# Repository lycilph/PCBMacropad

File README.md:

# PCBMacropad

Arduino pro micro pinout
* https://learn.sparkfun.com/tutorials/pro-micro--fio-v3-hookup-guide/hardware-overview-pro-micro
 
Kicad resources (for keyboards)
* https://github.com/joe-scotto/scottokeebs/tree/main/Extras/ScottoKicad
* https://github.com/ebastler/marbastlib

Tap drill chart (for self tapping screws into pla)
* https://mae.ufl.edu/designlab/Lab%20Assignments/EML2322L%20Tap%20Drill%20Chart.pdf
* From here: https://www.reddit.com/r/3dprinter/comments/fnlmps/hole_size_for_selftapping_screws/

Keycaps
* https://www.printables.com/model/109679-cherry-mx-low-profile-keycap
* https://www.thingiverse.com/thing:4186055
* https://www.printables.com/model/405230-blank-xda-keycap-mx-compatible
* https://www.printables.com/model/397962-blank-xda-profile-keycaps?ref=makerluis.com

Arduino simulator
* https://wokwi.com/projects/new/arduino-uno
* https://app.cirkitdesigner.com/

Idea for v2:
* https://github.com/dekuNukem/duckyPad-Pro

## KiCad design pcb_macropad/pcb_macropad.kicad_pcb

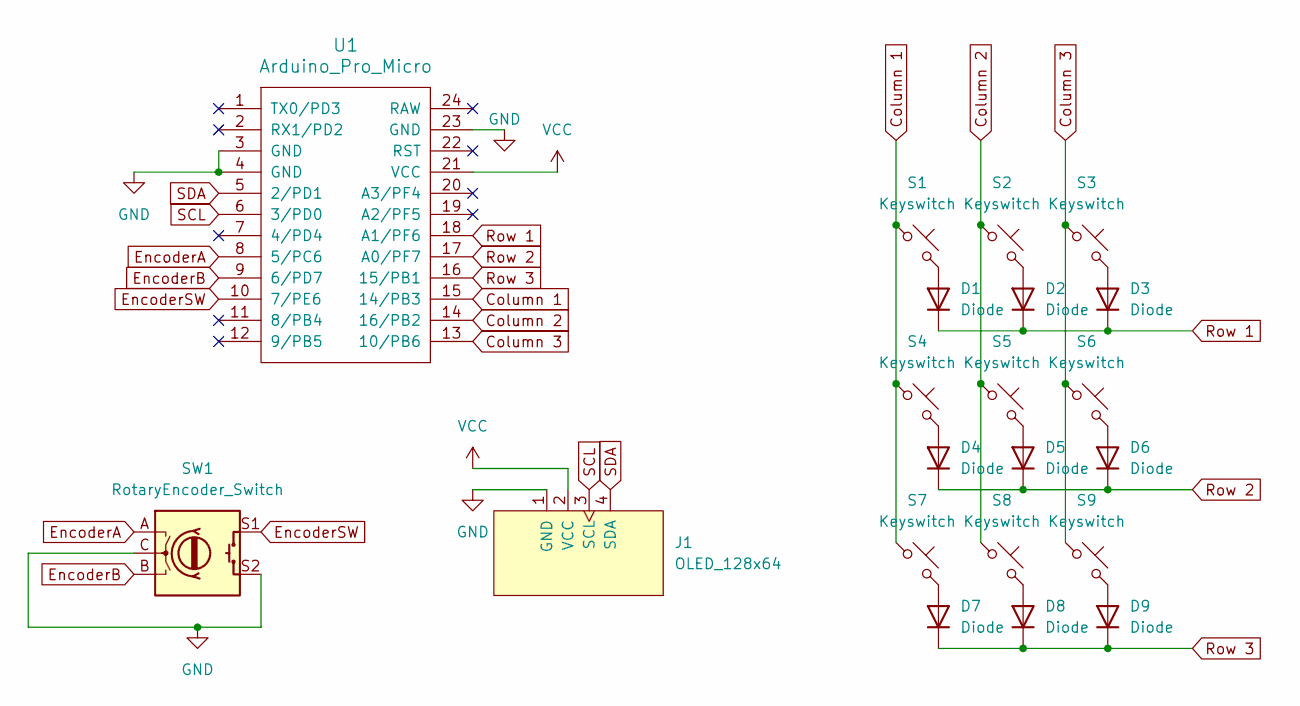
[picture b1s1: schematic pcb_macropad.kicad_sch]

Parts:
D1, D2, D3, D4, D5, D6, D7, D8, D9: Diode; Diode_DO-35
J1: OLED_128x64; 128x64OLED
S1, S2, S3, S4, S5, S6, S7, S8, S9: Keyswitch; MX_PCB_1.00u
SW1: RotaryEncoder_Switch; RotaryEncoder_Alps_EC11E-Switch_Vertical_H20mm
U1: Arduino_Pro_Micro

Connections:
Column 1: S1.1, S4.1, S7.1, U1.15 (14/PB3)
Column 2: S2.1, S5.1, S8.1, U1.14 (16/PB2)
Column 3: S3.1, S6.1, S9.1, U1.13 (10/PB6)
EncoderA: SW1.A, U1.8 (5/PC6)
EncoderB: SW1.B, U1.9 (6/PD7)
EncoderSW: SW1.S1, U1.10 (7/PE6)
GND: J1.1 (GND), SW1.C, SW1.S2, U1.3 (GND), U1.4 (GND), U1.23 (GND)
unnamed: D1.2 (A), S1.2
unnamed: D2.2 (A), S2.2
unnamed: D3.2 (A), S3.2
unnamed: D4.2 (A), S4.2
unnamed: D5.2 (A), S5.2
unnamed: D6.2 (A), S6.2
unnamed: D7.2 (A), S7.2
unnamed: D8.2 (A), S8.2
unnamed: D9.2 (A), S9.2
Row 1: D1.1 (K), D2.1 (K), D3.1 (K), U1.18 (A1/PF6)
Row 2: D4.1 (K), D5.1 (K), D6.1 (K), U1.17 (A0/PF7)
Row 3: D7.1 (K), D8.1 (K), D9.1 (K), U1.16 (15/PB1)
SCL: J1.3 (SCL), U1.6 (3/PD0)
SDA: J1.4 (SDA), U1.5 (2/PD1)
VCC: J1.2 (VCC), U1.21 (VCC)

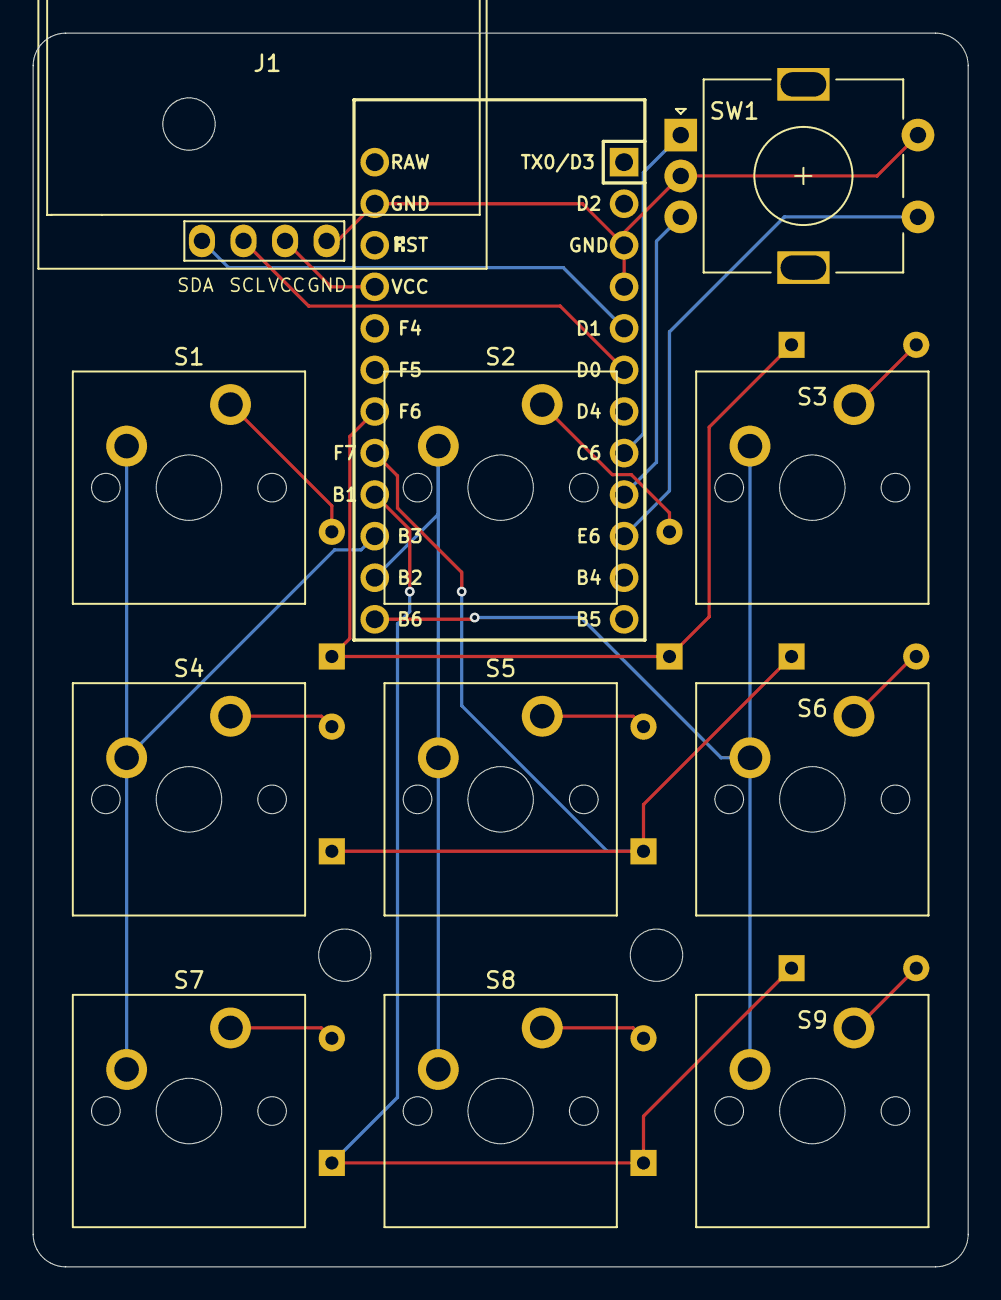
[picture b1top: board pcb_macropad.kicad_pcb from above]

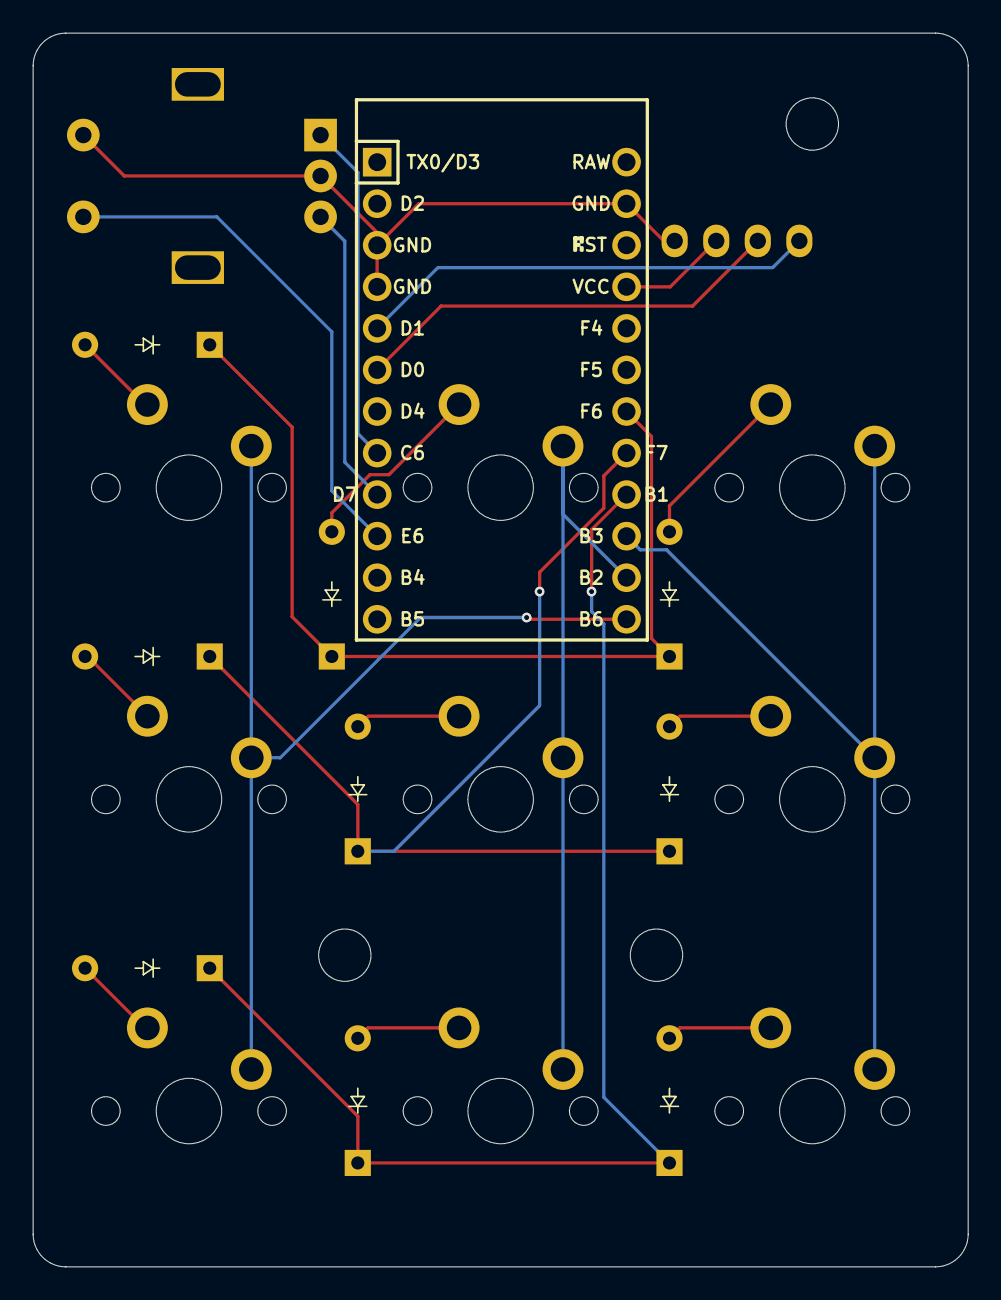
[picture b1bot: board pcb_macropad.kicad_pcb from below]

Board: 2 copper layers, 57.1 x 75.4 mm, 21 parts (10 on the bottom side), 22 nets.

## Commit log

2024-06-27 PCB draft done
2024-08-16 Backups
2024-08-19 Add burn in protection for the oled
2024-08-19 Graphics updated
2025-07-03 Making the macropad configurator app
2025-07-03 Added the traybar icon
2025-07-03 Added a log on the main winwo
2025-07-04 Working on the short edit view/view model
2025-07-04 Working on state management
2025-07-04 Loading data implemented
2025-07-04 Working on the shortcuts manager etc.
2025-07-08 Added the keyboardhook and adding/removing of shortcuts
2025-07-08 Making script compilation threaded
2025-07-08 Shortcut script compilation is not async
2025-07-08 Working on the configuration of the macropad buttons
2025-07-09 Added code for hid commucation
2025-07-09 Two-way communication via rawhid is now working
2025-07-10 Working on the macropad v2 firmware
2025-07-11 Working on the arduino v2 sketch
2025-07-12 Updating the arduino sketch
2025-07-12 Bugs in the sending of keys...
2025-07-15 V4 of the hid communication tests is now successfull
2025-07-16 Updating the arduino sketch and starting the implementation in the configurator app
2025-07-17 Running out of memory/ram on arduino, changing to ssd1306ascii
2025-07-17 Saving and loading on the arduino is now fixed and the first communication with the macropad is working
2025-07-18 Working on the configuration view
2025-07-19 Working on the configurator app
2025-08-04 Working on the ui
2025-08-05 Added settings (including serialization)
2025-08-05 Added the option to hide on close
2025-08-05 Working on the shortcuts and layers
2025-08-07 Working on editing layers and shortcuts
2025-08-07 Small bugfix
2025-08-08 Working on the edit shortcut view/viewmodel
2025-08-08 Added a dummy communication service
2025-08-08 Added the keyboard hook
2025-08-08 Added scripts to the shortcuts
2025-08-08 Compiling script on launch
2025-08-08 The application can now load configuration from the macropad
2025-08-09 It is now possible to upload new configurations to the macropad
2025-08-09 Added a command to "factory"-reset the macropad
2025-08-09 Added scripting commands
2025-08-11 Working on adding a master script, that all the other scripts references implicitly
2025-08-11 Cleaning up (removed test projects in both visual studio and arduino)
2025-08-11 Small bugfix for oled not inverting
2025-08-13 Cleaned up and added a master script that all other scripts include implicitly
2025-08-15 Add option to run on windows startup. Also fixed oled invert functionality on macropad
2025-08-21 Cleaning up code, and added a reset of the arduino, when a new configuration is uploaded
2025-08-21 Startup message on arduino is now displaying correctly
2025-08-21 Added a couple of functions to the scripting host
2025-08-21 Added a single instance check
2025-08-22 App now starts minimized if launched during windows startup
2025-08-22 Data now written to file, when changes are made
2025-08-26 Fixed a bug in detecting multiple instances
2025-08-26 Added toast notification functionality to scripts
2025-08-26 Added functionality to change sound device from scripts
2025-08-26 Start hidden (bad solution, but works)
2025-08-28 Fixed not being able to start ms-teams when running a script through the keyboard hook
2025-08-28 Windows can now be shown in the foreground (even when launched through a keyboard hook)
2025-08-28 Trying to deploy clickonce to github
2025-08-28 Click once deployment test
2025-08-28 More clickonce deployment
2025-08-28 Updated settings view
2025-08-28 Test of clickonce updates
